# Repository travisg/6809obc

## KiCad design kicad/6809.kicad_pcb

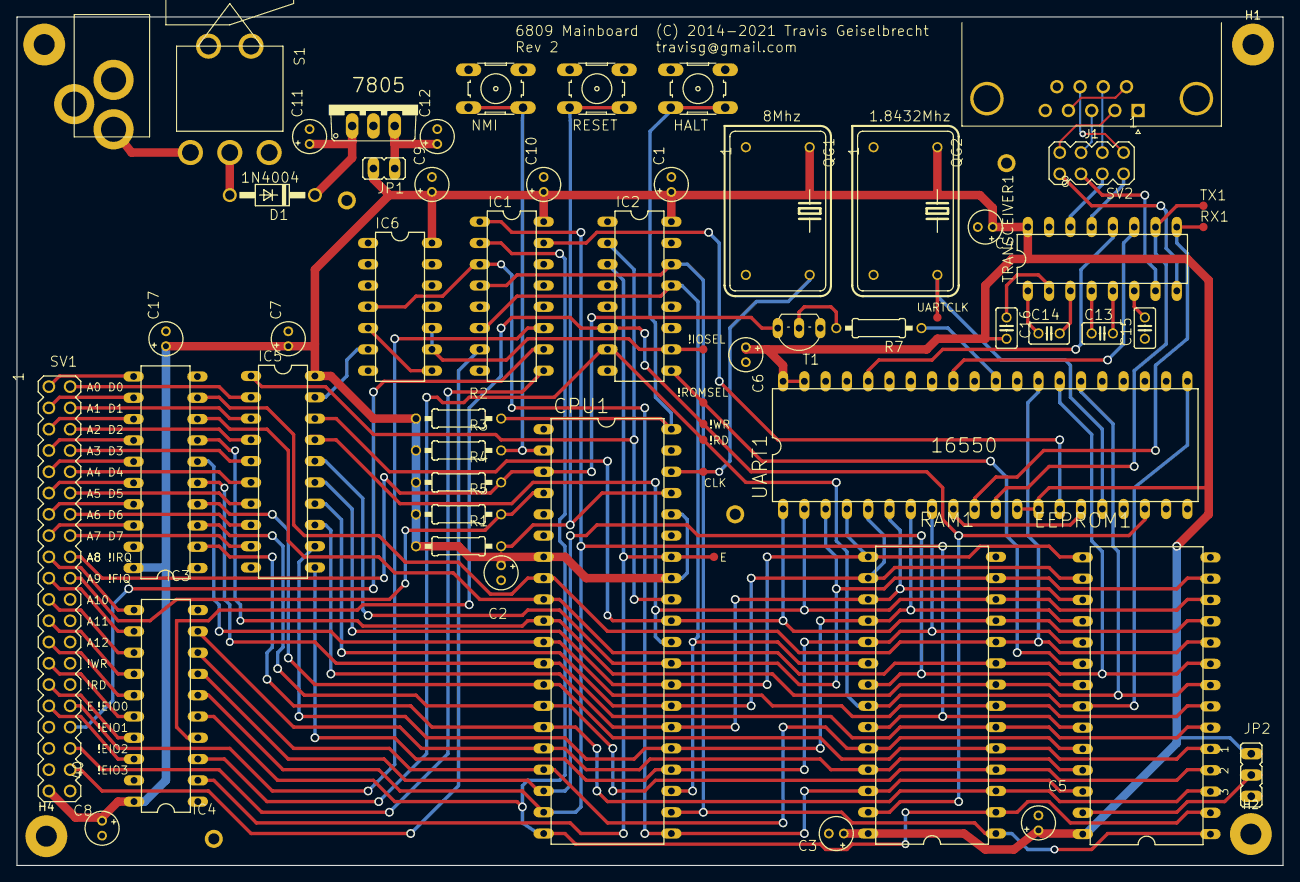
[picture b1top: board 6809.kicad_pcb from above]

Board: 2 copper layers, 151.1 x 101.3 mm, 66 parts (0 on the bottom side), 97 nets.

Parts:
C1, C2, C3, C4, C5, C6, C7, C8, C9, C10, C11, C12, C17: 10uF; E1,8-4
C13, C14, C15, C16: 1uF; C025-025X050
CN1: 2.1MMJACK; PJ-102A
CPU1: 68B09P; DIL40
D1: 1N4004; DO41-10
EEPROM1: 28C256; DIL28
H1, H2, H3, H4: MountingHole; MountingHole_2.5mm_Pad
IC1: 74138N; DIL16
IC2: 74139N; DIL16
IC3, IC4: 74541N; DIL20
IC5: 74245N; DIL20
IC6: 7400N; DIL14
IC7: 7805; TO220V
J1: DB9_Male_MountingHoles; DSUB-9_Male_Horizontal_P2.77x2.84mm_EdgePinOffset7.70mm_Hou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
JP1: JP1E; JP1
JP2: JP2E; JP2
QG1: 8Mhz; DIL14S
QG2: 1.8432Mhz; DIL14S
R1, R2, R3, R4, R5: 10K; 0207_10
R7: 4.7K; 0207_10
RAM1: 62256; DIL28
RX1: TPTP10R; TP10R
S1: ST1-1
S2: NMI; B3F-10XX
S3: RESET; B3F-10XX
S4: HALT; B3F-10XX
SV1: EXT; MA20-2
SV2: MA04-2
T1: PN2222; TO92-EBC-OVAL
TP1, TP2, TP3, TP4: TPPAD1-13; P1-13
TP5, TP6, TP7, TP8, TP10, TP11, TP12: TPTP10R; TP10R
TRANSCEIVER1: MAX232; DIL16
TX1: TPTP10R; TP10R
UART1: 16550; DIL40

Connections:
/6809_1/A0_EXT: IC3.11, SV1.1
/6809_1/A1_EXT: IC3.12, SV1.3
/6809_1/A2_EXT: IC3.13, SV1.5
/6809_1/A3_EXT: IC3.14, SV1.7
/6809_1/A4_EXT: IC3.15, SV1.9
/6809_1/A5_EXT: IC3.16, SV1.11
/6809_1/A6_EXT: IC3.17, SV1.13
/6809_1/A7_EXT: IC3.18, SV1.15
/6809_1/A8_EXT: IC4.11, SV1.17
/6809_1/A9_EXT: IC4.12, SV1.19
/6809_1/A10_EXT: IC4.13, SV1.21
/6809_1/A11_EXT: IC4.14, SV1.23
/6809_1/A12_EXT: IC4.15, SV1.25
/6809_1/E: CPU1.34, IC2.3, IC4.2, TP12.TP
/6809_1/E_EXT: IC4.18, SV1.31
/6809_1/R/~W: CPU1.32, IC2.2, IC5.1
/6809_1/~EXTIOSEL: IC5.19, IC6.6
/6809_1/~EXTIOSEL0: IC1.11, SV1.32
/6809_1/~EXTIOSEL1: IC1.10, SV1.34
/6809_1/~EXTIOSEL2: IC1.9, SV1.36
/6809_1/~EXTIOSEL3: IC1.7, SV1.38
/6809_1/~FIRQ: CPU1.4, R5.1, SV1.20
/6809_1/~HALT: CPU1.40, R2.1, S4.3, S4.4
/6809_1/~IOSEL: IC2.10, IC6.9, IC6.10, TP7.TP
/6809_1/~NMI: CPU1.2, R3.1, S2.3, S2.4
/6809_1/~RD~_EXT: IC4.17, SV1.29
/6809_1/~RESET: CPU1.37, R1.1, S3.3, S3.4
/6809_1/~ROMSEL: EEPROM1.20, IC2.9, TP8.TP
/6809_1/~WR~_EXT: IC4.16, SV1.27
/6809_2/CTS: SV2.2, TRANSCEIVER1.13
/6809_2/RTS: SV2.4, TRANSCEIVER1.14
/6809_2/RXD: SV2.8, TRANSCEIVER1.8
/6809_2/TXD: SV2.6, TRANSCEIVER1.7
A0: CPU1.8, EEPROM1.10, IC3.9, RAM1.10, UART1.28
A1: CPU1.9, EEPROM1.9, IC3.8, RAM1.9, UART1.27
A2: CPU1.10, EEPROM1.8, IC3.7, RAM1.8, UART1.26
A3: CPU1.11, EEPROM1.7, IC3.6, RAM1.7
A4: CPU1.12, EEPROM1.6, IC3.5, RAM1.6
A5: CPU1.13, EEPROM1.5, IC3.4, RAM1.5
A6: CPU1.14, EEPROM1.4, IC3.3, RAM1.4
A7: CPU1.15, EEPROM1.3, IC3.2, RAM1.3
A8: CPU1.16, EEPROM1.25, IC4.9, RAM1.25
A9: CPU1.17, EEPROM1.24, IC4.8, RAM1.24
A10: CPU1.18, EEPROM1.21, IC4.7, RAM1.21
A11: CPU1.19, EEPROM1.23, IC1.1, IC4.6, RAM1.23
A12: CPU1.20, EEPROM1.2, IC1.2, IC4.5, RAM1.2
A13: CPU1.21, EEPROM1.26, IC1.3, IC6.4, RAM1.26
A14: CPU1.22, EEPROM1.1, IC1.4, IC2.14, RAM1.1
A15: CPU1.23, IC1.6, IC2.13, RAM1.20
D0: CPU1.31, EEPROM1.11, IC5.18, RAM1.11, UART1.1
D1: CPU1.30, EEPROM1.12, IC5.17, RAM1.12, UART1.2
D2: CPU1.29, EEPROM1.13, IC5.16, RAM1.13, UART1.3
D3: CPU1.28, EEPROM1.15, IC5.15, RAM1.15, UART1.4
D4: CPU1.27, EEPROM1.16, IC5.14, RAM1.16, UART1.5
D5: CPU1.26, EEPROM1.17, IC5.13, RAM1.17, UART1.6
D6: CPU1.25, EEPROM1.18, IC5.12, RAM1.18, UART1.7
D7: CPU1.24, EEPROM1.19, IC5.11, RAM1.19, UART1.8
GND: C1.-, C2.-, C3.-, C4.-, C5.-, C6.-, C7.-, C8.-, C9.-, C10.-, C11.-, C12.-, C15.1, C17.-, CN1.RING, CN1.RING_SW, CPU1.1, CPU1.39, EEPROM1.14, IC1.5, IC1.8, IC2.1, IC2.8, IC2.15, IC3.1, IC3.10, IC3.19, IC4.1, IC4.10, IC4.19, IC5.10, IC6.1, IC6.2, IC6.7, IC6.12, IC6.13, IC7.2, J1.0, J1.5, JP2.3, QG1.7, QG2.7, RAM1.14, S2.1, S2.2, S3.1, S3.2, S4.1, S4.2, SV1.40, T1.E, TP1.TP, TP2.TP, TP3.TP, TP4.TP, TRANSCEIVER1.15, UART1.19, UART1.20, UART1.22, UART1.25, UART1.35, UART1.37, UART1.38
unnamed: C11.+, D1.C, IC7.1
unnamed: C12.+, IC7.3, JP1.1
unnamed: C13.1, TRANSCEIVER1.4
unnamed: C13.2, TRANSCEIVER1.5
unnamed: C14.1, TRANSCEIVER1.1
unnamed: C14.2, TRANSCEIVER1.3
unnamed: C15.2, TRANSCEIVER1.6
unnamed: C16.1, TRANSCEIVER1.2
unnamed: CN1.TIP, S1.P$1
unnamed: CPU1.38, QG1.8, TP11.TP
unnamed: D1.A, S1.P$2
unnamed: EEPROM1.27, JP2.2
unnamed: IC5.2, SV1.2
unnamed: IC5.3, SV1.4
unnamed: IC5.4, SV1.6
unnamed: IC5.5, SV1.8
unnamed: IC5.6, SV1.10
unnamed: IC5.7, SV1.12
unnamed: IC5.8, SV1.14
unnamed: IC5.9, SV1.16
unnamed: IC6.5, IC6.8
unnamed: J1.2, SV2.7
unnamed: J1.3, SV2.5
unnamed: J1.4, J1.6
unnamed: J1.7, SV2.3
unnamed: J1.8, SV2.1
unnamed: QG2.8, TP10.TP, UART1.16
unnamed: R7.1, UART1.30
unnamed: R7.2, T1.B
unnamed: RX1.TP, TRANSCEIVER1.9, UART1.10
unnamed: TRANSCEIVER1.10, TX1.TP, UART1.11
unnamed: TRANSCEIVER1.11, UART1.32
unnamed: TRANSCEIVER1.12, UART1.36
unnamed: UART1.9, UART1.15
VCC: C1.+, C2.+, C3.+, C4.+, C5.+, C6.+, C7.+, C8.+, C9.+, C10.+, C16.2, C17.+, CPU1.7, CPU1.33, CPU1.36, EEPROM1.28, IC1.16, IC2.16, IC3.20, IC4.20, IC5.20, IC6.14, JP1.2, JP2.1, QG1.14, QG2.14, R1.2, R2.2, R3.2, R4.2, R5.2, RAM1.28, SV1.39, TRANSCEIVER1.16, UART1.12, UART1.13, UART1.39, UART1.40
~IOSEL0: IC1.15, UART1.14
~IRQ: CPU1.3, R4.1, SV1.18, T1.C
~RD: EEPROM1.22, IC2.7, IC4.3, RAM1.22, TP6.TP, UART1.21
~WR: IC2.6, IC4.4, RAM1.27, TP5.TP, UART1.18

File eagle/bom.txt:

Partlist exported from /home/geist/eagle/6809/6809.sch at 7/14/14 10:38 PM

Qty Value        Device          Package       Parts                                                  Description                                                                              
1                JP1E            JP1           JP1                                                    JUMPER                                                                                   
1                JP2E            JP2           JP2                                                    JUMPER                                                                                   
1                MA04-2          MA04-2        SV2                                                    PIN HEADER                                                                               
1   1.8432Mhz    QG5860          DIL14S        QG2                                                    CRYSTAL RESONATOR                                                                        
5   10K          R-US_0207/10    0207/10       R1, R2, R3, R4, R5                                     RESISTOR, American symbol                                                                
13  10uF         CPOL-USE1.8-4   E1,8-4        C1, C2, C3, C4, C5, C6, C7, C8, C9, C10, C11, C12, C17 POLARIZED CAPACITOR, American symbol                                                     
1   16550        16550           DIL40         UART                                                                                                                                            
1   1N4004       1N4004          DO41-10       D1                                                     DIODE                                                                                    
4   1uF          C-US025-025X050 C025-025X050  C13, C14, C15, C16                                     CAPACITOR, American symbol                                                               
1   2.1MMJACKTHM 2.1MMJACKTHM    PJ-102A       CN1                                                    2.1mm x 5.5mm THM DC jack with internal switch. Digikey part #PJ-102A, 4UCON part #05537 
1   28C256       28C256          DIL28         EEPROM                                                 8K x 8 EEPROM                                                                            
1   4.7K         R-US_0207/10    0207/10       R7                                                     RESISTOR, American symbol                                                                
1   62256        62256           DIL28         RAM                                                    32KB sram                                                                                
1   68B09P       6809            DIL40         CPU                                                    MICROCONTROLLER/MEMORY DEVICE                                                            
1   74HC00N      74HC00N         DIL14         IC6                                                    Quad 2-input NAND gate                                                                   
1   74HC138N     74HC138N        DIL16         IC1                                                    3-line to 8-line DECODER/DEMULTIPLEXER                                                   
1   74HC139N     74HC139N        DIL16         IC2                                                    Dual 2-line to 4-line DECODER/DEMULTIPLEXER                                              
1   74HC245N     74HC245N        DIL20         IC5                                                    Octal BUS TRANSCEIVER, 3-state                                                           
2   74HC541N     74HC541N        DIL20         IC3, IC4                                               Octal BUFFER and LINE DRIVER, 3-state                                                    
1   7805TV       7805TV          TO220V        IC7                                                    Positive VOLTAGE REGULATOR                                                               
1   8Mhz         QG5860          DIL14S        QG1                                                    CRYSTAL RESONATOR                                                                        
1   COM1         F09HP           F09HP         DE9                                                    SUB-D                                                                                    
1   EXT          MA20-2          MA20-2        SV1                                                    PIN HEADER                                                                               
1   HALT         10-XX           B3F-10XX      S4                                                     OMRON SWITCH                                                                             
1   MAX232       MAX232          DIL16         TRANSCEIVER                                            RS232 TRANSCEIVER                                                                        
1   NMI          10-XX           B3F-10XX      S2                                                     OMRON SWITCH                                                                             
1   PN2222       2N2222          TO92-EBC-OVAL T1                                                     NPN TRANSISTOR                                                                           
1   RESET        10-XX           B3F-10XX      S3                                                     OMRON SWITCH                                                                             
1   ST1-1        ST1-1           ST1-1         S1                                                                                                                                              
4   TPPAD1-13    TPPAD1-13       P1-13         TP1, TP2, TP3, TP4                                     Test pad                                                                                 
9   TPTP10R      TPTP10R         TP10R         RX, TP5, TP6, TP7, TP8, TP10, TP11, TP12, TX           Test pad

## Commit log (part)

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2014-07-19 revision 1 of the 6809 one board computer eagle cad files
2014-07-19 add license file for all of the contents of the repository
2014-07-19 [rom] initial checkin of some rom code
2014-07-23 [rom] add libihex submodule, build ihextobin, and use it to generate the bin file
2014-07-26 add .gitignore for eagle cad stuff
2016-10-28 [eagle] some work on a rev 2
2017-12-21 [rom] some rom tweakery
2017-12-21 [libihex] bump to newer version
2017-12-21 [rom][c] start to cobble together a C based rom
2017-12-21 WIP checkpoint C rom
2017-12-21 WIP monitor
2017-12-31 WIP move .S files to C, add compiler.h
2017-12-31 WIP compile as PIC
2017-12-31 WIP split things into more .c files
2017-12-31 WIP switch to monitor to using a tokenizer

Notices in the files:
kicad/6809.kicad_pcb:
(C) 2014-2021 Travis Geiselbrecht
